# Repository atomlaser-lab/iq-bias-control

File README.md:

# IQ Modulator Bias Control

This project implements a digital bias controller for an IQ modulator running in carrier-suppressed single-sideband (CS-SSB) mode.  It is based on [this paper](http://opg.optica.org/ao/abstract.cfm?uri=ao-62-1-1) which detailed an analog stabilisation scheme using the same technique.  Our arXiv submission, with more detail about our digital implementation and performance, can be found [here](https://arxiv.org/abs/2408.16678).  The basic idea is to add a low frequency signal to the main, high frequency signal used for CS-SSB and use the low frequency signal to measure the phase biases in the different Mach-Zehnder interferometers (MZIs) that make up the IQ modulator.  Whereas the original work used purely analog techniques, this project levarages the fast analog input/output capabilities of the Red Pitaya STEMlab 125-14 platform.  

# Software set up

  1. Clone both this repository and the interface repository at [https://github.com/atomlaser-lab/red-pitaya-interface](https://github.com/atomlaser-lab/red-pitaya-interface) to your computer.  

  2. Connect the Red Pitaya (RP) board to an appropriate USB power source (minimum 2 A current output), and then connect it to the local network using an ethernet cable.  Using SSH (via terminal on Linux/Mac or something like PuTTY on Windows), log into the RP using the hostname `rp-{MAC}.local` where `{MAC}` is the last 6 characters of the RP's MAC address which is written on the ethernet connector.  Your network may assign its own domain, so `.local` might not be the correct choice.  The default user name and password for RPs is `root`.  Once logged in, create two directories called `iq-bias-control` and `server`.

  3. From this repository, copy over all files in the 'software/programs/' directory to the `iq-bias-control` directory on the RP using either `scp` (from a terminal on your computer) or using your favourite GUI (I recommend WinSCP for Windows).  Also copy over the file `fpga/iq-bias-control.bit` to the `iq-bias-control` directory.  From the interface repository, copy over all files ending in '.py' and the file 'get_ip.sh' to the `server` directory on the RP.

  4. On the RP and in the `iq-bias-control` directory, compile the C programs.  You can compile these using the Makefile by running the command `make` with no arguments.  This will compile all the C programs in the directory.  

  5. In the `server` directory, change the privileges of `get_ip.sh` using `chmod a+x get_ip.sh`.  Check that running `./get_ip.sh` produces a single IP address (you may need to install dos2unix using `apt install dos2unix` and then run `dos2unix get_ip.sh` to make it work).  If it doesn't, run the command `ip addr` and look for an IP address that isn't `127.0.0.1` (which is the local loopback address).  There may be more than one IP address -- you're looking for one that has tags 'global' and 'dynamic'.  Here is the output from one such device:
   ```
   root@rp-f0919a:~# ip addr
   1: lo: <LOOPBACK,UP,LOWER_UP> mtu 65536 qdisc noqueue state UNKNOWN group default qlen 1
      link/loopback 00:00:00:00:00:00 brd 00:00:00:00:00:00
      inet 127.0.0.1/8 scope host lo
         valid_lft forever preferred_lft forever
      inet6 ::1/128 scope host 
         valid_lft forever preferred_lft forever
   2: eth0: <BROADCAST,MULTICAST,UP,LOWER_UP> mtu 1500 qdisc pfifo_fast state UP group default qlen 1000
      link/ether 00:26:32:f0:91:9a brd ff:ff:ff:ff:ff:ff
      inet 169.254.176.82/16 brd 169.254.255.255 scope link eth0
         valid_lft forever preferred_lft forever
      inet 192.168.1.109/24 brd 192.168.1.255 scope global dynamic eth0
         valid_lft 77723sec preferred_lft 77723sec
   3: sit0@NONE: <NOARP> mtu 1480 qdisc noop state DOWN group default qlen 1
      link/sit 0.0.0.0 brd 0.0.0.0
   ```
   The IP address we want here is the address `192.168.1.109` as it has the `global` tag, which is what `get_ip.sh` looks for.  If you have your RP connected directly to your computer it will not work and you will have to specify the IP address manually.

   6. Upload the bitstream to the FPGA by navigating to the `iq-bias-control` directory and running `cat iq-bias-control.bit > /dev/xdevcfg`.

   7. Start the Python server by navigating to the `iq-bias-control` directory and running `python3 /root/server/appserver.py`.  If you need to specify your IP address run instead `python3 /root/server/appserver.py <ip address>`.  The script will print the IP address it is using on the command line, saying `Listening on <IP address>`.

   8. On your computer in MATLAB, add the interface repository directory to your MATLAB path.

   9. Navigate to this repository's software directory (or add it to the MATLAB path), and create a new control object using `d = IQBiasControl(<ip address>)` where `<ip address>` is the IP address of the RP.  If the FPGA has just been reconfigured, set the default values using `d.setDefaults` and upload them using `d.upload`.  If you want to retrieve the current operating values use the command `d.fetch`.

   10. You can control the device using the command line, but the recommended method is to use the GUI.  Start the GUI by running the command `IQ_Bias_Control_GUI(d)`.  This will start up the GUI.  You can also run `IQ_Bias_Control_GUI(<ip address>)` if you don't have the `IQBiasControl` object in your workspace.

# Hardware set up

Connect the OUT1 and OUT2 signals to the I and Q modulation ports (order doesn't matter) on the IQ modulator.  If you want to use this with a high frequency signal as well, then you need a method of combining the low frequency signals from the Red Pitaya ($\Omega_{\rm LF}$) and the high frequency signals ($\Omega_{\rm HF}$).  The best option is to use diplexers as they have lower loss than simple power combiners.  Make sure that the output voltages/powers are within the specified tolerances of the device.  The OUT1 and OUT2 signals are already 90 degrees out of phase, so they don't need to go through a 90 degree hybrid.  You may want significant attenuation on the output ports so that the auxiliary signal is much weaker than the desired main signal.  Measure the output laser power using a photodiode of sufficient bandwidth, filter out the DC component using a high-pass filter or a bias tee, amplify as necessary, and connect to the IN1 connector.  On the LV setting the IN1 input can only measure a peak voltage of 1 V, or 10 dBm.  

Connect the slow analog outputs 0-2 to the IQ modulator's DC biases: see [this page](https://redpitaya.readthedocs.io/en/latest/developerGuide/hardware/125-14/extent.html) for the pinout.  You may need to amplify these signals (maximum output is 1.6 V) to get the right voltage range.  The slow analog outputs are pulse width modulation (PWM) outputs with a 250 MHz clock and 10 bits of resolution, so the PWM frequency is about 244 kHz.  You will likely want additional filtering on the outputs for driving the DC biases.  Take care if you use aluminium electrolytic capacitors for the filter, as the equivalent series resistance (ESR) can severely compromise filtering capabilities at high frequencies.  

Alternatively, you can build the included "shield" for the Red Pitaya that connects to the PWM analog outputs, filters them, and amplifies them to be in the range [0,14.6] V. The corner frequency is approximately 200 Hz, which suppresses the power at the fundamental PWM frequency of 244 kHz by about 57 dB.  Choosing different filtering capacitors will give you different suppression and bandwidths.  A KiCAD project is provided in the `board-design/` directory in addition to Gerber files in `board-design/generated/` for manufacturing.  We have had good experiences with JLCPCB in manufacturing boards.  Part lists `red-pitaya-pwm-shield.txt` and `additional-parts.txt` provide Digikey part numbers for components.

Digital inputs DIO0_N and DIO1_N provide additional control over feedback (see [this page](https://redpitaya.readthedocs.io/en/latest/developerGuide/hardware/125-14/extent.html)).  DIO0_N is a digital input that controls the sample-and-hold system and is OR'ed with the software sample-and-hold setting.  When high (3.3 V logic), it enables sample-and-hold.  DIO1_N is a digital input that can be used to turn off the RF output from the RP; when high (3.3 V logic), it turns off the RF output.

# Using the GUI

The GUI is best way to control the device.  There are four categories of device settings plus the application settings.

## Acquisition Settings

The idea behind this technique is to generate a low-frequency modulation signal at a few MHz, inject it into the IQ modulator, measure the laser power using a photodetector, and then demodulate that signal at the modulation frequency in both quadratures (in-phase I and quadrature-phase Q), and also to demodulate at twice the modulation frequency (both I and Q are provided).  Demodulation is implemented digitally by multiplying the input signal with a sinusoidally varying signal at the correct frequency but with a demodulation phase (1 and 2), and the result is then filtered using a CIC filter with a rate of $2^N$.  So under acquisition settings, "Modulation Freq" is the modulation frequency output from the RP, "Demod Phase 1" and "Demod Phase 2" are the demodulation phases at the modulation frequency and its second harmonic, "Log2(CIC Rate)" is $N$, and "Log2 of CIC shift" is an additional digital scaling factor that amplifies/attenuates the output signals by $2^M$ where $M$ is the integer given in the control.  The time step between filtered samples, and the equivalent bandwidth, is given at the bottom of the panel.

## Control

Assuming that the demodulation phases are properly set, the bias voltages on the IQ modulator should independently control each demodulated signal with very limited cross-coupling.  In reality, there can be significant cross-coupling.  To account for cross-coupling, we use a multi-dimensional integral control scheme.  For a vector of output voltages $\mathbf{v}$, a vector of signals $\mathbf{s}$, and a vector of set-points $\mathbf{r}$, we implement a control law as a 3x3 matrix $K$ such that $\mathbf{v} = K\int(\mathbf{r} - \mathbf{s})dt$.  The integer values for the control matrix $K$ are given as K11, K12, etc, and these can be negative to allow for opposite polarity responses.  Additionally, to account for possibly different orders of magnitude of gain reponse, each output voltage has its own "divisor" to allow for fixed-point arithmetic.  Therefore, the output voltage $v_1$ is $v_1 = 2^{-N_1}(K_{11}s_1 + K_{12}s_2 + K_{13}s_3)$, where $N_1$ is labelled as "Divisor 1", and similarly for the other rows 2 and 3.  

Other controls are reasonably straightforward.  The `Enable` switch turns the controller on, and the `Hold` switch holds the outputs at the current values.  The switch `Disable output on hold?` turns off the output DAC when the hold is enabled.  If it is set to `On`, then when the hold is engaged (either from software or from the digital input) it switches off the output DAC.  This can be used if the presence of the $\Omega_{\rm LF}$ signal is detrimental to the experiment during a pulse sequence.  

The different set points allow for stabilising the signals about a non-zero value, and the upper and lower limits at the bottom limit the PMW output voltages (values are prior to any amplifiers you may add).

## Manual Control

The voltage biases DC1, DC2, and DC3 adjust the phases of the three MZIs in the IQ modulator and thus allow for CS-SSB as well as all sorts of other, undesired output modes.  Unfortunately, simply by measuring the optical power it is fundamentally impossible to determine what frequency is on the output of the IQ modulator, as all single-frequency operation generates a steady DC value on the photodiode.  The manual control allows the user to get close to CS-SSB operation, and then the controller will ideally keep it in that mode.

DC1, DC2, and DC3 are output voltages from 0 to 1.6 V that should be connected to the appropriate pins on the IQ modulator.  These values can be changed using the sliders or spinners.  If using the arrows on the spinners, the DC increment can be changed to allow for coarser or finer changes.  Note that the minimum DC increment is 1.6 mV.

The `Correct PWM` button can be used to adjust the manual PWM values so that they are equal to the mean PWM values achieved by feedback.  When feedback is enabled, clicking `Correct PWM` will record 100 ms of the output PWM values and then it will adjust the manual values to match the mean values.

## FIFO Settings

The measurements are recorded in first-in, first-out (FIFO) buffers on chip, and then that data can be retrieved and displayed.  What data gets recorded can be changed by the user using the `FIFO 1`, `FIFO 2`, etc drop-down menus.  If they are set to `In`, the measurements after demodulation and filtering are recorded, and if they are set to `Out` the PWM values are recorded.  `In` values are plotted on the left Y axis, and `Out` values are plotted on the right Y axis.  The checkboxes control what values are plotted on the graph.

## Application Settings

`Upload` uploads all displayed settings to the RP.  `Fetch` grabs the values off of the RP and updates the display.  `Fetch Data` grabs `Acquisition Samples` number of samples after demodulation and displays that on the plot.  Change the display limits using `YLim1` for the left-hand axis and `YLim2` for the right-hand axis.  

`Auto-Update` uploads the device configuration anytime a parameter is changed.

`Auto-Fetch Data` continuously uploads parameters and fetches demodulated data and displays it on the plot.  The update time is given in `Plot Update Time` in milliseconds.  You can change the parameters as it grabs data in order to optimise the bias values.

You can also save and load bias control configurations using the `Load` and `Save` buttons.

# How to determine gain parameters

The best way to get the right gain parameters is to measure the response of the system to a change in the bias voltage, and then to calculate the gain parameters from that.  There is a script called `automatically_set_feedback.m` in the `software/` folder which does this task.  You may need to alter the script to suit your IQ modulator and system.  You will also need the MATLAB Statistics toolbox and the Optimization toolbox for the functions `range` and `fsolve`, respectively.  It is recommended that you step through the script one section at a time, checking the results as you go.  Here is how the script works.

**FEEDBACK MUST BE DISABLED TO RUN THIS SCRIPT**

You will need a rough idea of what the right bias voltages are, first.  The best way to do this is to use a scanning optical cavity, but beating the output field from the IQ modulator with a reference at a different frequency can also be used.  Adjust the manual voltages until you are close to CS-SSB operation.  Roughly, the algorithm is to iteratively adjust DC1 and DC2 to minimize the amount of power in the carrier, and then to adjust DC3 to choose the positive or negative sideband as desired.  

Once you are close, set the desired modulation frequency (multiples of 5 MHz appear to be problematic), the sample rate, and any scalings.  The first step is to measure the 2f demodulation phase.  This is done by varying the DC3 voltage and the 2f demodulation phase, and then looking at what demodulation phase gives the largest amplitude change to the 2f demodulated signal: this is the optimum demodulation phase.

The next step is to do a fine scan over the DC3 bias at the optimum demodulation phase to find the biases at which the 2f signal amplitude crosses zero.  There are two voltages, and for the ixBlue IQ modulator that we use the voltage that corresponds to the positive sideband is the higher voltage near 0.9 V.  This gets a fine-tuned measurement.

Next, we perform a scan over the DC2 bias and the 1f demodulation phase to determine the optimal phase.  Again, we look at what phase gives the maximum amplitude change to the 1f Q signal.  By definition, this minimizes cross-coupling with the 1f I signal.

With the correct 1f demodulation phase, a fine scan is applied to determine the voltages at which the 1f I and Q signals cross zero.  There will likely be two zero crossings for each of the I and Q signals, so you will need to use additional information, such as an optical cavity, to determine which ones correspond to CS-SSB mode.

We then do two steps of small variations about the bias voltages that we have measured to give zero signal.  We then fit the measurements to a linear response to get a transfer matrix $G$ (the slope of the lines) and new zero crossing voltages $\mathbf{z}$.  We then re-measure the responses around these new zero-crossing voltages, which gives a final transfer matrix $G$.  You should check that the plots of this transfer matrix show the measured signals going through zero when the DC voltages are at their nominal values.

We then measure the dynamic response by applying a step change to the DC voltages and measuring the time-dependent relaxation of the measured signals.  

The feedback matrix is then calculated by starting with a target matrix $K_t$ and computing $K = G^{-1}K_t$.  For critical damping, the elements of $K_t$ should be $[K_t]_{ii} = [\Gamma]^{1/2}_{ii}/2$.

# Troubleshooting

## CS-SSB operation lost

If your scanning optical cavity is showing that CS-SSB operation has been lost, then it is highly likely that the bias lock has been lost.  This can occur if the locking system has been kicked out of its capture range by, for instance, a large temperature change.  Alternatively, charge can accumulate on the electrodes and in the LiNBO3 that affects the optimum bias voltages.  Similarly, charge can be freed by the optical field that then affects the response.

  1. DISABLE THE LOCK.  If you leave the lock on while changing the biases, it will do very weird things.
  2. If, after disabling the lock, the system returns to near CS-SSB operation, try re-engaging the lock.
  3. If this doesn't work, disable the lock, manually re-optimise the biases, re-optimise the lock parameters, and then re-lock.

## GUI unresponsive

If the GUI appears unresponsive, in that changing GUI parameters such as biases or the lock enable status appears to do nothing:

  1. IS THE LOCK ENGAGED?  If the lock is engaged and you try to change the bias voltages, it might appear that nothing is happening because the lock forces the system into CS-SSB operation.
  2. IS AUTO_UPDATE DISABLED?  If Auto-Update is disabled, then changed parameters on the GUI will not be uploaded to the device.  Set Auto-Update to "On".
  3. Has the Red Pitaya been disconnected from the network?  Bring up the PuTTY or terminal window that is logged into the Red Pitaya.  If the server is running, use CTRL-Z to suspend it.  If the terminal throws an error, like "Connection lost" or somesuch, then reconnect to the Red Pitaya (on PuTTY you can right-click on the window's title bar and click "Reconnect").  Navigate back to the `iq-bias-control` directory using `cd iq-bias-control` and start the Python server again using `python3 /root/server/appserver.py`.  If the running server suspended without error, bring it back to the foreground using the command `fg`.
  4. Is the figure data in the GUI not updating?  This is probably just an error in the timer used for non-command-line-blocking fetching of the data.  Set Auto-Fetch Data to "Off" and then "On" again.

# Creating the project

When creating the project, use Vivado 2023.2.

To create the project, clone the repository to a directory on your computer, open Vivado, navigate to the fpga/ directory (use `pwd` in the TCL console to determine your current directory and `cd` to navigate, just like in Bash), and then run `source make-project.tcl` which will create the project files under the directory `basic-project`.  If you want a different file name, open the `make-project.tcl` file and edit the line under the comment `# Set the project name`.  This should create the project with no errors.  It may not correctly assign the AXI addresses, so you will need to open the address editor and assign the `PS7/AXI_Parse_0/s_axi` interface the address range `0x4000_000` to `0x7fff_ffff`.

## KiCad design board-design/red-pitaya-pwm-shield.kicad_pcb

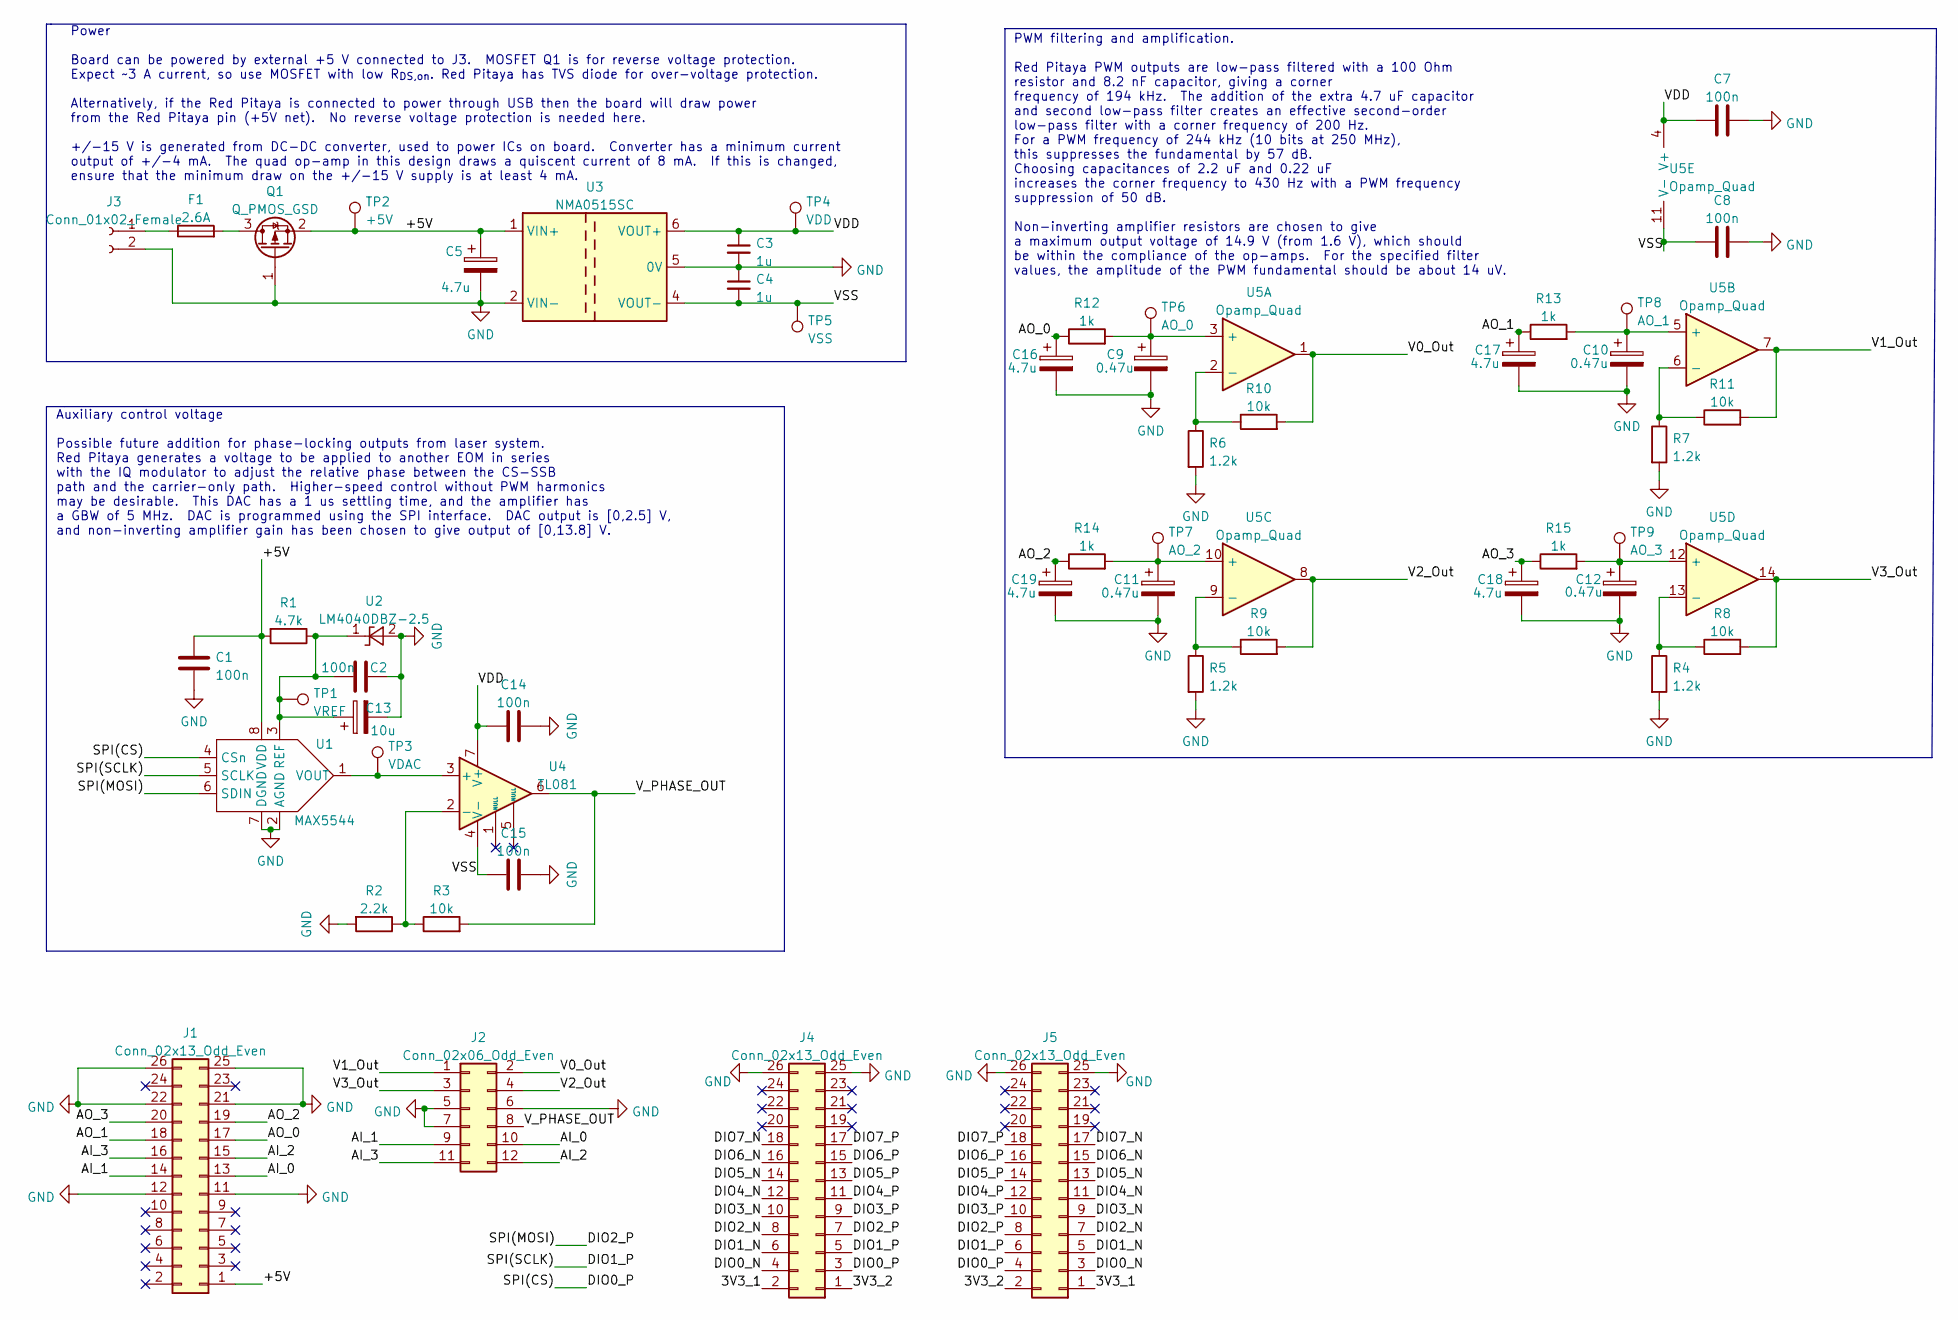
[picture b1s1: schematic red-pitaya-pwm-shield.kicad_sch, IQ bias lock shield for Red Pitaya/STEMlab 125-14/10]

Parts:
C1, C2, C7, C8, C14, C15: 100n; C_1206_3216Metric_Pad1.33x1.80mm_HandSolder; Digikey Part Number 399-C1206C104K5RAC7800CT-ND
C3, C4: 1u; C_1206_3216Metric_Pad1.33x1.80mm_HandSolder; Digikey Part Number 1276-1097-1-ND
C5, C16, C17, C18, C19: 4.7u; C_1206_3216Metric_Pad1.33x1.80mm_HandSolder; Digikey Part Number 1276-3179-1-ND
C9, C10, C11, C12: 0.47u; C_1206_3216Metric_Pad1.33x1.80mm_HandSolder; Digikey Part Number 1276-1118-1-ND
C13: 10u; CP_Radial_D5.0mm_P2.00mm; Digikey Part Number 732-8937-1-ND
F1: 2.6A; R_1206_3216Metric_Pad1.30x1.75mm_HandSolder; Digikey Part Number 2315-SBF32252ASTPCT-ND
J1, J4: Conn_02x13_Odd_Even; PinSocket_2x13_P2.54mm_Vertical; Digikey Part Number SAM11136-ND
J2: Conn_02x06_Odd_Even; PinSocket_2x06_P2.54mm_Vertical; Digikey Part Number 732-61300621821-ND
J3: Conn_01x02_Female; TerminalBlock_bornier-2_P5.08mm; Digikey Part Number 732-10955-ND
J5: Conn_02x13_Odd_Even; PinSocket_2x13_P2.54mm_Vertical; Digikey Part Number 732-61302621821-ND
Q1: Q_PMOS_GSD; SOT-23-3; Digikey Part Number DMP3099L-7DICT-ND
R1: 4.7k; R_1206_3216Metric_Pad1.30x1.75mm_HandSolder; Digikey Part Number 311-4.70KFRCT-ND
R2: 2.2k; R_1206_3216Metric_Pad1.30x1.75mm_HandSolder; Digikey Part Number RMCF1206JT2K20CT-ND
R3, R8, R9, R10, R11: 10k; R_1206_3216Metric_Pad1.30x1.75mm_HandSolder; Digikey Part Number 1292-WR12X103JTLCT-ND
R4, R5, R6, R7: 1.2k; R_1206_3216Metric_Pad1.30x1.75mm_HandSolder; Digikey Part Number RMCF1206JT1K20CT-ND
R12, R13, R14, R15: 1k; R_1206_3216Metric_Pad1.30x1.75mm_HandSolder; Digikey Part Number RMCF1206JT1K00CT-ND
TP1: VREF; TestPoint_Pad_D1.0mm
TP2: +5V; TestPoint_Pad_D1.0mm
TP3: VDAC; TestPoint_Pad_D1.0mm
TP4: VDD; TestPoint_Pad_D1.0mm
TP5: VSS; TestPoint_Pad_D1.0mm
TP6: AO_0; TestPoint_Pad_D1.0mm
TP7: AO_2; TestPoint_Pad_D1.0mm
TP8: AO_1; TestPoint_Pad_D1.0mm
TP9: AO_3; TestPoint_Pad_D1.0mm
U1: MAX5544; SOIC-8_3.9x4.9mm_P1.27mm; Digikey Part Number MAX5544CSA+-ND
U2: LM4040DBZ-2.5; SOT-23; Digikey Part Number 576-1047-1-ND
U3: NMA0515SC; Converter_DCDC_Murata_NMAxxxxSC_THT; Digikey Part Number 811-1453-5-ND
U4: TL081; SOIC-8_3.9x4.9mm_P1.27mm; Digikey Part Number 296-TL081HIDRCT-ND
U5: Opamp_Quad; SOIC-14_3.9x8.7mm_P1.27mm; Digikey Part Number MC33079DR2GOSCT-ND

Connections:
/3V3_1: J4.2, J5.1
/3V3_2: J4.1, J5.2
/+5V: C1.2, C5.1, J1.1, Q1.2 (S), R1.2, TP2.1, U1.8 (VDD), U3.1 (VIN+)
/AI_0: J1.13, J2.10
/AI_1: J1.14, J2.9
/AI_2: J1.15, J2.12
/AI_3: J1.16, J2.11
/AO_0: C16.1, J1.17, R12.1
/AO_1: C17.1, J1.18, R13.1
/AO_2: C19.1, J1.19, R14.1
/AO_3: C18.1, J1.20, R15.1
/DIO0_N: J4.4, J5.3
/DIO0_P: J4.3, J5.4, U1.4 (CSn)
/DIO1_N: J4.6, J5.5
/DIO1_P: J4.5, J5.6, U1.5 (SCLK)
/DIO2_N: J4.8, J5.7
/DIO2_P: J4.7, J5.8, U1.6 (SDIN)
/DIO3_N: J4.10, J5.9
/DIO3_P: J4.9, J5.10
/DIO4_N: J4.12, J5.11
/DIO4_P: J4.11, J5.12
/DIO5_N: J4.14, J5.13
/DIO5_P: J4.13, J5.14
/DIO6_N: J4.16, J5.15
/DIO6_P: J4.15, J5.16
/DIO7_N: J4.18, J5.17
/DIO7_P: J4.17, J5.18
/V0_Out: J2.2, R10.2, U5.1
/V1_Out: J2.1, R11.2, U5.7
/V2_Out: J2.4, R9.2, U5.8
/V3_Out: J2.3, R8.2, U5.14
/VDD: C3.1, C7.1, C14.2, TP4.1, U3.6 (VOUT+), U4.7 (V+), U5.4 (V+)
/VSS: C4.2, C8.1, C15.2, TP5.1, U3.4 (VOUT-), U4.4 (V-), U5.11 (V-)
/V_PHASE_OUT: J2.8, R3.2, U4.6
GND: C1.1, C2.2, C3.2, C4.1, C5.2, C7.2, C8.2, C9.2, C10.2, C11.2, C12.2, C13.2, C14.1, C15.1, C16.2, C17.2, C18.2, C19.2, J1.11, J1.12, J1.21, J1.22, J1.25, J1.26, J2.5, J2.6, J2.7, J3.2, J4.25, J4.26, J5.25, J5.26, Q1.1 (G), R2.2, R4.2, R5.2, R6.2, R7.2, U1.2 (AGND), U1.7 (DGND), U2.2 (A), U3.2 (VIN-), U3.5 (0V)
unnamed: C9.1, R12.2, TP6.1, U5.3 (+)
unnamed: C10.1, R13.2, TP8.1, U5.5 (+)
unnamed: C11.1, R14.2, TP7.1, U5.10 (+)
unnamed: C12.1, R15.2, TP9.1, U5.12 (+)
unnamed: C2.1, C13.1, R1.1, TP1.1, U1.3 (REF), U2.1 (K)
unnamed: F1.1, J3.1
unnamed: F1.2, Q1.3 (D)
unnamed: R2.1, R3.1, U4.2 (-)
unnamed: R4.1, R8.1, U5.13 (-)
unnamed: R5.1, R9.1, U5.9 (-)
unnamed: R6.1, R10.1, U5.2 (-)
unnamed: R7.1, R11.1, U5.6 (-)
unnamed: TP3.1, U1.1 (VOUT), U4.3 (+)

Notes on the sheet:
Auxiliary control voltage Possible future addition for phase-locking outputs from laser system. Red Pitaya generates a voltage to be applied to another EOM in series with the IQ modulator to adjust the relative phase between the CS-SSB path and the carrier-only path. Higher-speed control without PW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
PWM filtering and amplification. Red Pitaya PWM outputs are low-pass filtered with a 100 Ohm resistor and 8.2 nF capacitor, giving a corner frequency of 194 kHz. The addition of the extra 4.7 uF capacitor and second low-pass filter creates an effective second-order low-pass filter with a corner fre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
Power Board can be powered by external +5 V connected to J3. MOSFET Q1 is for reverse voltage protection. Expect ~3 A current, so use MOSFET with low R_{DS,on}. Red Pitaya has TVS diode for over-voltage protection. Alternatively, if the Red Pitaya is connected to power through USB then the board wi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

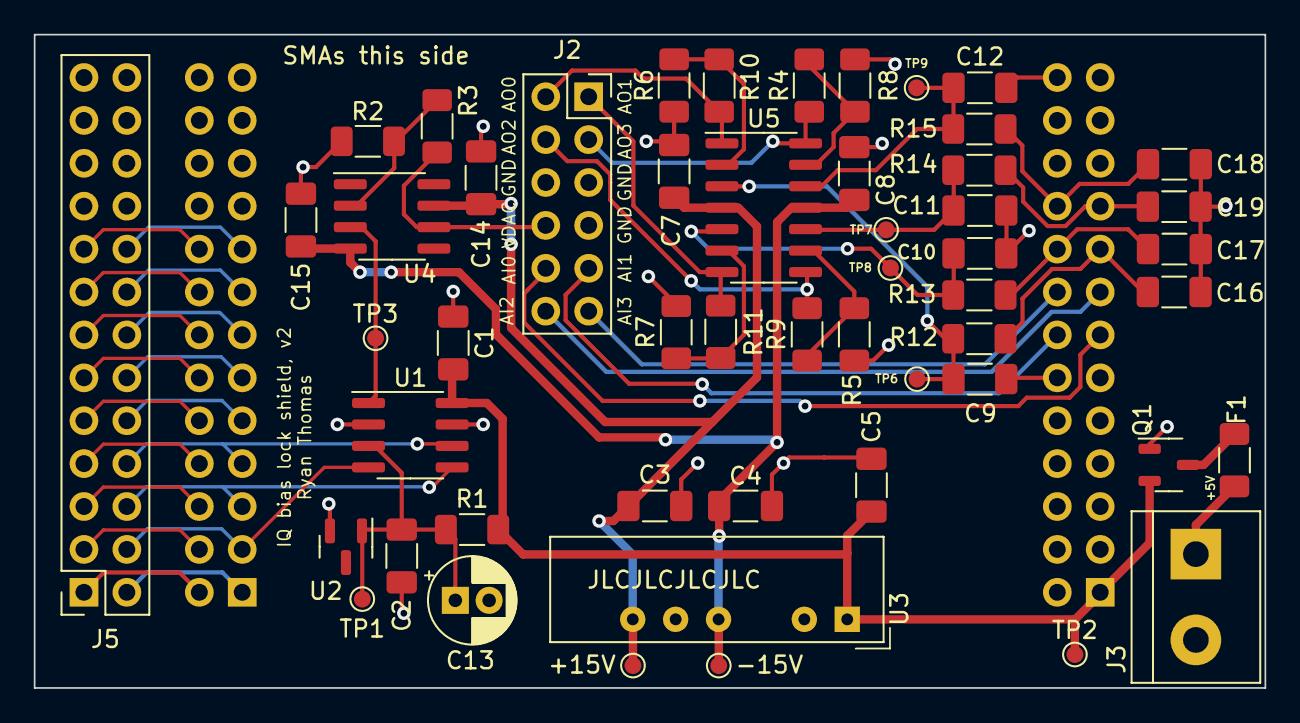
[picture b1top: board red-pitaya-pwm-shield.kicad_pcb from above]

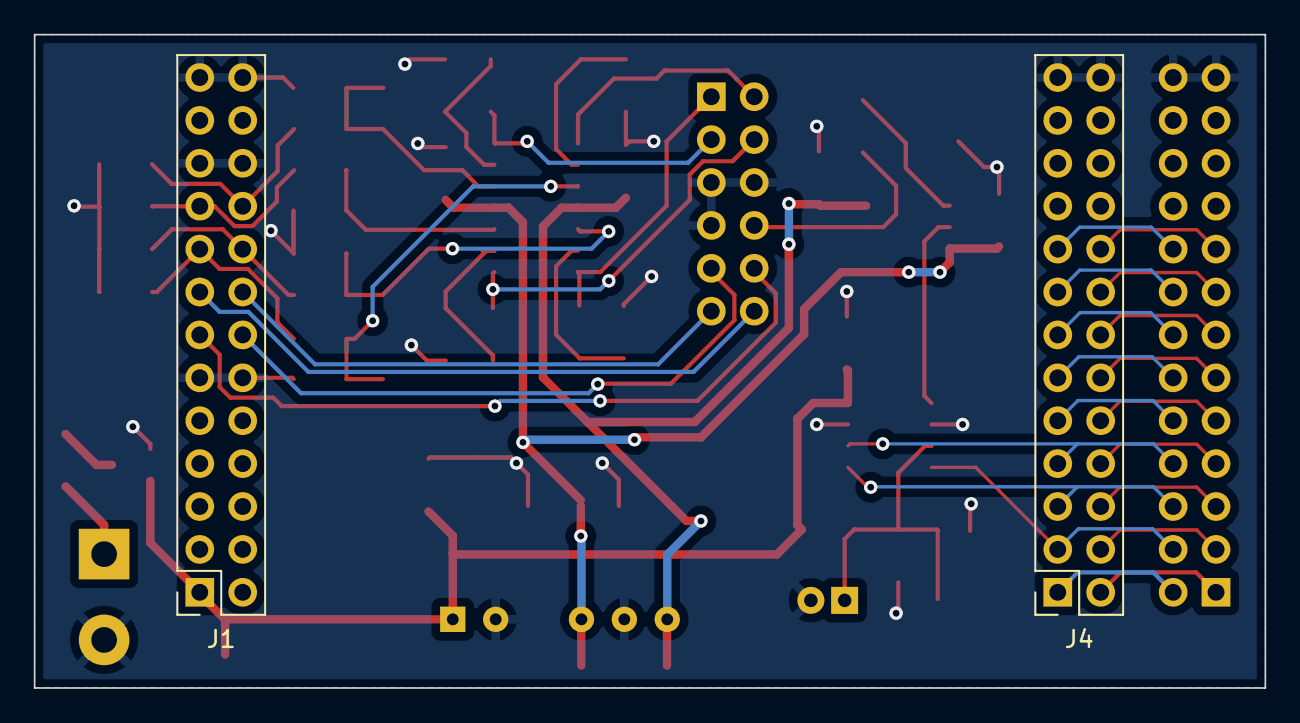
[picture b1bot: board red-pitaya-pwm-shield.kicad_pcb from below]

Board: 2 copper layers, 72.9 x 38.7 mm, 54 parts (2 on the bottom side), 48 nets.

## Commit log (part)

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2023-11-07 Initial commit of project, originally from the basic design
    Needs testing to make sure TCL recreates project
2023-11-07 Added new packages, FIFO handler
2023-11-08 Modified DeviceControl, removed other classes
2023-11-08 Added FIFO signals, untested
2023-11-08 Added data saving C program, MATLAB methods. Untested
2023-11-08 Added Demodulator module + testbench. Works in simulation.
    Demodulator handles the generation of the modulation signal for
    driving the IQ modulator, and then also handles the demodulation
    of that signal at cos(w_m t), sin(w_m t), and cos(2*w_m t).
2023-11-09 Increased filter output width
2023-11-09 Updated PID controller to better version for this project
2023-11-11 Created PWM module, simulated but untested
2023-11-11 Started working on GUI
2023-11-14 Minor update to topmod adding PID signals
2023-11-14 Added block memory for debugging ADC data
2023-11-14 Minor bug fix to DeviceControl. Memory reading works
2023-11-19 Started to add control to project
2023-11-19 Added PWM outputs and manual changes to PWM outputs
2023-11-22 Upgraded IP for 2023.2
2023-12-19 Added some matlab calculations
2023-12-19 Added C function and MATLAB code to measure response to varying bias values
2023-12-21 Added simulation functions, visualisation app
2023-12-21 Added functions to scan over bias values, also to optimise bias values and phases
2023-12-21 Added max voltage for C voltage scan function
2023-12-22 Continued work on app
2023-12-22 Updated DeviceControl to upload/fetch using a single TCP transaction
    Also added an auto_retry function
2023-12-22 Some additions to optimise_biases
2023-12-22 Fixed bugs in GUI
2023-12-22 Minor changes to slice viewer
2023-12-23 Added output scaling
2024-01-03 Started to clean up the demodulation system, simplify VHDL code
2024-01-03 Finished clean-up. Changed PWM to 10 bits. Tested
    Topmod is now better organized as the demodulation stuff is in a
    dedicated component. I also increased the PWM width to 10 bits for
    PWM 0 - 3. PWM 4 is fixed at 0 now.
    Both quadratures of both the 1f and 2f signals are recorded now.
2024-01-10 Added PID stuff to GUI. Doesn't currently work
2024-01-11 Fixed bug in control module instantiation, control works now
    The problem with control not working was that a new signal called
    "clk" had been defined and was used as the input clock signal
    for the control module, but "clk" was not connected to anything.
    Connected input clock to adcClk instead.
    We definitely need some diagnostic capabilities for optimising the lock
2024-01-12 Redid PID MATLAB control to use modules.
    MATLAB now uses PID modules for controlling PID parameters for
    ease of expansion and use.
    Also changed how the upload and fetch procedures work. They need
    the new version of the red-pitaya-interface (v1.3).
2024-01-12 Fixed problems with software and hardware code. Now works.
2024-01-15 Added saving/loading functions, fixed some bugs in GUI
2024-01-16 Control over 3 biases implemented. CIC shift now allowed to be negative
2024-01-16 Changed PID signals to be more array-based
2024-01-16 Updated software. Untested.
2024-01-16 Added/tested FIFO routing. PID VHDL array has timing issues
    So it looks like when signals are defined as arrays that Vivado tries
    to keep the signals together, and this creates routing issues.
    When the pid register signals were all separate, routing didn't
    take too long and the design met timing constraints. Now that they
    are all arrays of arrays of arrays, timing is not met. This needs
    testing
2024-01-16 Updated README.
    I also checked that the design builds in the same time with the
    same issues if pid registers and other signals are NOT arrays.
    So clearly it's just the complicated and probably not very
    well optimised design.
2024-01-29 Created coupled integral controller in VHDL and software
    Simulated VHDL design, and it works. Untested on hardware.
    I have not updated the GUI yet.
2024-01-29 Minor changes to software
2024-01-29 Changed GUI for coupled control. Untested on device
2024-01-29 Generated bitstream with some bug fixes
2024-01-29 Minor updates and fixes
2024-01-30 Added automatic feedback measurement. Untested
2024-01-30 Got automatic gain measurement working. Multi-dim feedback works
2024-01-30 Added automatic gain measurement
2024-01-31 Added Demodulator_tb file, updated topmod_tb. Minor change to feedback calc.
    Vivado won't simulate Demodulator.vhd as is because it has some
    undefined issue with the shift_right operation at the very end
    of the CIC filters. Fixing the value to a constant solves the
    problem, though.
2024-02-01 Changed control module to use a single multiplier
2024-02-01 Built and tested single-multiplier coupled control design. Works
2024-02-02 Added capability to measure dynamic response to a step change
    This allows the user to estimate the time constants/low pass freqs
    associated with the actuator.
2024-02-02 Updated picture of GUI
2024-02-02 Added proportional gain. Untested
2024-02-02 Fixed bugs
2024-02-03 Synthesized and wrote software for prop gain. Can't get it to lock.
2024-02-03 Fixed bug in loadobj, changed display of automatic gain setting
2024-02-04 Got proportional gain working. Not sure about it.
    I can get proportional gain to work, but it definitely has some
    issues. It's not a straightforward 2nd order system as a result
    so I'm not sure what I'm really getting out of the extra complexity.
2024-03-22 Mostly minor updates
2024-03-26 Minor fixes
2024-03-27 Added functions to read data from spectrum analyzer
2024-04-12 Added phase correction to design. Not built or tested
    Optimum suppression of the carrier does not occur when the I/Q 1f
    signals are at 0. I hypothesize that this is due to a different
    phase difference between the I/Q driving signals fro the RP compared
    to the MW source. I added an extra DDS unit to drive the Q signal at
    a slightly different phase from 90 degrees.
2024-04-12 Minor changes
2024-04-12 Fixed bugs, implemented phase correction
2024-04-13 Added software for independent output scale factors
2024-04-13 Added VHDL, bitstream for differential output scaling
2024-04-15 Test design for measuring carrier suppression
2024-04-15 Minor change to IP file
2024-04-16 Added demodulation signal at f1 + f2
2024-04-16 Fixed some bugs and added analysis code
2024-04-17 Changed save data and jump response C functions to use variable number of FIFOs
2024-04-19 Added hold capability, ADC switch
2024-04-19 Removed superfluous IP, added ADC selector switch, wrote bitstream
2024-04-24 Added correct_pwm() method, minor changes elsewhere
2024-05-03 Added PCB design with bipolar DAC.
2024-05-03 Mostly routed board design
2024-05-03 Switched to unipolar DAC, routed board, assigned parts. Generated BOM
2024-05-03 Added generated PDFs
2024-05-06 Updated text on schematic, fixed position of headers on PCB
2024-05-06 Added Makefile, minor changes to readme
2024-05-07 Added fuse, removed Zener diode. Added test points. Generated Gerber files
2024-05-07 Added silkscreen text for order number placement
2024-05-09 Fixed bug in measuring linear responses. PWM voltages were not reset to zero
2024-05-09 Increased PWM width to 14 bits. Built, tested bitstream
2024-05-17 Minor changes and bug fixes
2024-05-20 Minor changes for new board
2024-05-21 Added 12 and 14 bit PWM bitstreams, some minor updates to software
2024-05-27 Added SPI driver for aux DAC, code for running it. Not built or tested
2024-05-27 Fixed bugs, built bitstream. Aux DAC not tested
2024-05-29 Updated README and added some images
2024-05-31 Minor update to automatic gain script
2024-05-31 Added function to auto script to look for zero closest to current values
2024-06-03 Started work on fixing problem with spontaneous unlocking
    I suspect that the unlocking behaviour that has been seen upstairs
    is due to overflow in the pidAccumulate signal in Control.vhd. Changed
    the width of the signal from 34 bits to 48 bits. Unbuilt and untested.
2024-06-03 Created bitstream with increased accumulate width
2024-06-05 Fixed a bug in Control related to timing
    Not enough time was allowed for multiplier outputs to be latched
    into the output. This somehow caused K33 outputs to end up on the
    PWM1 output.
2024-06-05 Added some matlab simulation files for PWM filtering
2024-06-10 Minor change to matlab simulation files
2024-06-11 Updated board design with better low-pass filter
2024-06-12 Updated Control, added SPI test bench
2024-06-16 Testing timing constraints
    Added constraint to eliminate timing requirements for the adcClk
    and sysClk paths. Also added a trigger for the demodulator filter
    change that isn't being driven by the filterConfig register.
2024-06-25 Swapped timing back to no false paths
2024-06-25 Fixed SPI data for DAC
2024-06-27 Added phase measurement module, built bitstream, untested
    Added phase measurement module to measure phase of 2*mod_freq signal
    that should be present after SHG
2024-07-23 Minor updates to existing matlab sim files, added phase error calc
2024-07-23 Added SPI to existing IQ design
2024-07-23 Added SPI functionality, updated MATLAB code, simulated, built bitstream
2024-07-24 Updated TCL script
2024-07-24 Regenerated bitstream with Vivado 2023.2
2024-07-25 Fixed memory access bug?
2024-07-25 Added bitstream
2024-07-25 Disabled SPI1 on PS7 block. Maybe this releases SPI resources?
2024-07-25 Fixed aux DAC conversion factor, added SPI period parameter
2024-07-25 Rearranged topmod, added DDS hold
    Added a DDS hold input to turn off DAC outputs, and also to link
    that to when the control is held. This should allow the bias
    controller to be paused briefly during pulses
2024-07-26 Eliminated use of PS SPI, changed board.
    SPI accessed through PS is not able to be used in programmable
    logic since the ports are not accessible. Switched to using
    3 pins from the E1 connector. Changed PCB to match.
2024-07-31 Added code + built bitstream for phase lock at second harmonic
    Significant modification to design to allow for phase measurement
    and locking. Added a module PhaseControl which comprises a phase
    measurement module, a phase unwrapping module, and a PID controller.
    Tested this module in simulation and it seems to work.
    I have assumed for the moment that the phase lock actuator
    is the 4th PWM output. This should get changed in the future
2024-08-01 Fixed some bugs in superclass handling
2024-08-01 Fixed memory access bug in new FIFOs. Added function to generate testing AXI data
2024-08-02 Minor fixes to software classes
2024-08-02 Added I/Q data readout, reorganized register addresses.
2024-08-02 Fixed bugs with new registers. Had to increase MAP_SIZE in c functions
2024-08-02 Re-factored C code to use unified function definitions
2024-08-02 Was missing the Q part of the I/Q FIFO data. Fixed.
2024-08-02 Added error reporting for data fetching
2024-08-03 Fixed bugs in C programs, added phase jump and analysis programs
2024-08-03 Changed phase width in FPGA, kept CORDIC width the same. Reorganized software
2024-08-04 Changed FIFO signals to avoid some simulation errors
2024-08-04 Added status register to monitor FIFO empty signals
2024-08-04 Fixed FIFO buffer reset issue
2024-08-04 Updated phase unwrapping module
2024-08-08 Changed PID module with divisors for each gain coefficient
    Also expanded size of measurements to try and avoid integer overflow
    Also added ability to lock to Q measurement rather than phase in
    case of low SNR.
2024-08-08 Fixed bug in phase jump analysis
2024-08-08 Added switch to allow phase lock to drive aux dac or PWM
2024-08-09 Fixed bug in calculating real phase lock gains
2024-08-09 Fixed some bugs involved in moving to aux DAC for phase control
2024-08-09 Aux DAC data now recorded in FIFO, correct data conversions applied in software
2024-08-10 Fixed type error with aux DAC
2024-08-27 Renamed DeviceControl object, added comments, improved README
2024-09-06 Updated TCL and bitstream
